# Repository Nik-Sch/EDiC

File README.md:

# EDiC - Educational Digital Computer
SystemVerilog simulation of an 8 bit discrete TTL CPU I am building for fun. The final CPU will be similar to Ben Eaters Project with some differences and the following features:
- I printed prototype PCBs that reassembles 830 Breadboards with some improvements.
- Two general purpose registers.
- ALU with `add/sub`, `AND`, `XOR` and left/right shift operations
- 512 byte instruction EEPROM (256 byte instruction, 256 immediate values)
- 256 byte program SRAM
- 8bit input and output registers

Full documentation is available as my [masters thesis](thesis/thesis.pdf).

## Update 08.03.2022 - EDiC is finished
The EDiC is finished and plays snake ;)

## Update 25.10.2021 - new name - new future
This project is getting a revival as I am rebuilding it with a few key changes and improvements.
It will get a real clock, one big multilayer PCB and stack pointer, 16bit ram/rom addressing and a lot more.

## Update 21.01.2021 - 8bit-CPU is finished!
  
- I debugged a lot of tiny bugs todo with writeEnable and especially clockEnable signals
- Mounted all PCBs to look nice

## Update 15.01.2021
<details><summary>First program got executed!</summary>
  
  - I finished building everything and after about a week of endless debugging bugfixing the first program ran correctly.
  - The gif below shows how the CPU executes 6² and outputs the result which is shown in hexadecimal (6²=36=0x24).

</details>

## Update 22.12.2020
<details><summary>Update of the final(ish) layout:</summary>
  
  - I finished and interconnected all of the data path + bus, except for the PC at the bottom.
  - The ALU + regset + SRAM is fully functional with some debugging effort like pulling up all connections to the 5V CMOS SRAM which has an higher voltage requirement for high level inputs.
  - Half of the control logic has wires and I decided to swap the two control boards for better interconnection.

</details>

## Update 13.12.2020
<details><summary>First picture of the final(ish) layout:</summary>
  
  - On top of all boards is the clock module which is basically the clock module by Ben Eater with 555 timers which features an automatic clock which speed is settable by a potentiometer an a manual, debounced clock pulse with a push button. I also added an SR latch for a halt signal which is resettable by a push button to be used as input to the CPU.
  - Red shows the ALU with two 4 bit adders on the left side (with one aluOp MUX. The top right board is a variable width shifter build with three 8 bit MUXs.
  For enabling left/right shift the last ALU board includes two MUXs to reverse the input and the final two aluOp MUXs.
  - Purple shows the register set on the left with a MUX for the A input of the ALU and one MUX + Tristate Transceiver to the bus.
  The bottom board will include LEDs for the registers and the right board includes aluOut register + Tristate, LEDs and register clock enable logic.
  - The blue encircled board contains the RAM module with an memory address register, the sockeled instruction EEPROM + SRAM.
  - Green will be the control logic with two instruction decode EEPROMs (for 16 control bits) + instruction register on the left.
  The right board includes a 4bit step register for the multicycle control + incrementor (4bit half adder) + logic for external control signals like the halt signal.
  - The orange boards finally include the program counter + incrementor + Tristate Transceiver and load from bus MUX.

</details>

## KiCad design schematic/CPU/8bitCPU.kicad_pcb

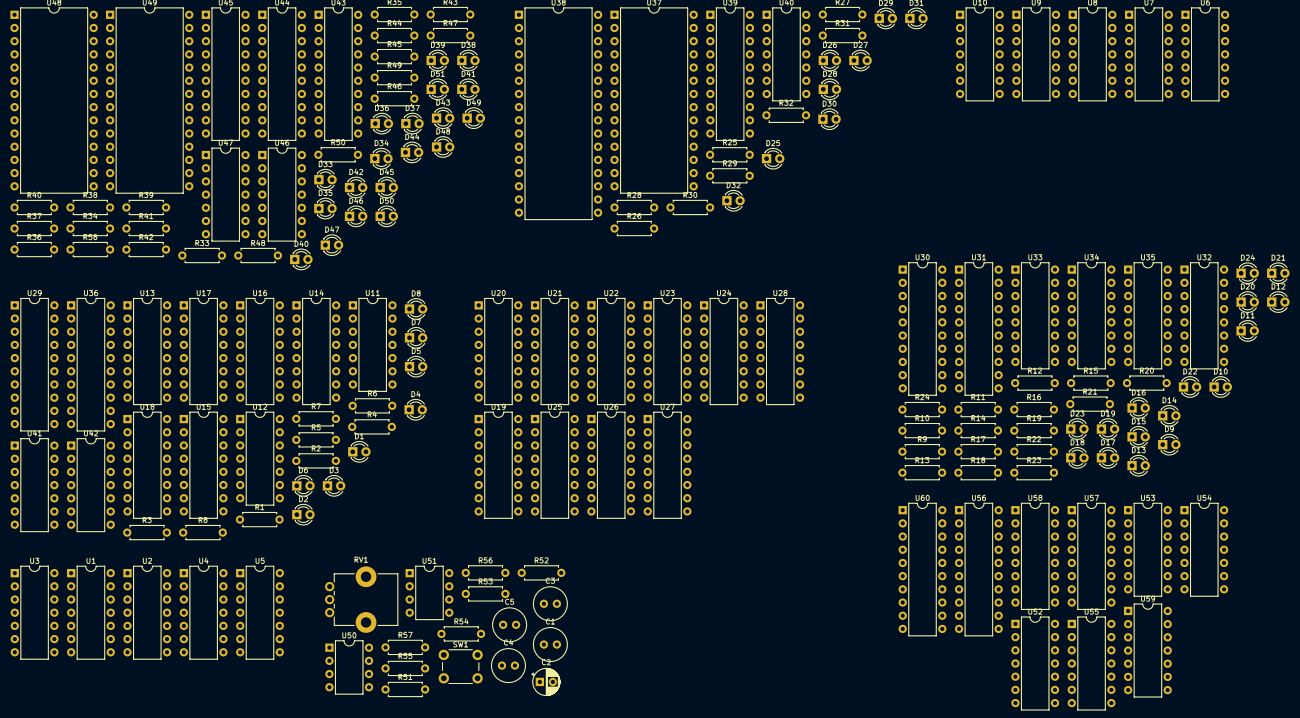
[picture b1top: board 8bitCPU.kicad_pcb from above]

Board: 2 copper layers, 176 parts (0 on the bottom side), 306 nets, no tracks yet.

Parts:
C1, C3: 0.01u; C_Radial_D6.3mm_H5.0mm_P2.50mm
C2: 0.1u; CP_Radial_D5.0mm_P2.50mm
C4, C5: 0.1u; C_Radial_D6.3mm_H5.0mm_P2.50mm
D1, D2, D3, D4, D5, D6, D7, D8, D9, D10, D11, D12, D13, D14, D15, D16, D17, D18, D19, D20, D21, D22, D23, D24, D25, D26, D27, D28, D29, D30, D31, D32, D45, D47, D48, D49, D50: LED; LED_D3.0mm
D33, D51: instrNWE; LED_D3.0mm
D34: instrSel; LED_D3.0mm
D35: aluNOE; LED_D3.0mm
D36: aluYNWE; LED_D3.0mm
D37: reg0NWE; LED_D3.0mm
D38: reg1NWE; LED_D3.0mm
D39: regBusSel; LED_D3.0mm
D40: regBusNOE; LED_D3.0mm
D41: aluSel; LED_D3.0mm
D42: marNWE; LED_D3.0mm
D43: ramWE; LED_D3.0mm
D44: ramOE; LED_D3.0mm
D46: ramSelect; LED_D3.0mm
R1, R2, R3, R4, R5, R6, R7, R8, R9, R10, R11, R12, R13, R14, R15, R16, R17, R18, R19, R20, R21, R22, R23, R24, R25, R26, R27, R28, R29, R30, R31, R32, R33, R34, R35, R36, R37, R38, R39, R40, R41, R42, R43, R44, R45, R46, R47, R48, R49, R50, R52, R53, R54, R57, R58: 1k; R_Axial_DIN0207_L6.3mm_D2.5mm_P7.62mm_Horizontal
R51, R55: 10M; R_Axial_DIN0207_L6.3mm_D2.5mm_P7.62mm_Horizontal
R56: 1M; R_Axial_DIN0207_L6.3mm_D2.5mm_P7.62mm_Horizontal
RV1: 1M; Potentiometer_Bourns_PTV09A-1_Single_Vertical
SW1: SW_Push; SW_PUSH_6mm
U1, U3, U6, U8, U11, U12, U47, U52, U54: 74LS86; DIP-14_W7.62mm
U2, U4, U7, U9, U46, U53, U55: 74LS08; DIP-14_W7.62mm
U5, U10, U41, U42, U59: 74LS32; DIP-14_W7.62mm
U13, U14, U15, U16, U17, U18, U19, U20, U21, U22, U23, U24, U25, U26, U27, U28, U32, U33, U57, U58: 74LS157; DIP-16_W7.62mm
U29, U30, U31, U39, U43: 74LS377; DIP-20_W7.62mm
U34, U35: 74LS257; DIP-16_W7.62mm
U36, U60: 74LS245; DIP-20_W7.62mm
U37, U48, U49: 28C64; DIP-28_W15.24mm
U38: AS6C1008-55PCN; DIP-32_W15.24mm
U40: 74LS00; DIP-14_W7.62mm
U44, U45, U56: 74LS273; DIP-20_W7.62mm
U50, U51: NA555P; DIP-8_W7.62mm

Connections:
/Alu/Adder0/Bit1/Cin: U3.4, U4.4, U5.3
/Alu/Adder0/Bit2/Cin: U3.9, U4.9, U5.6
/Alu/Adder0/Bit3/Cin: U3.12, U4.12, U5.8
/Alu/Adder0/b0: U1.2, U2.2, U11.3
/Alu/Adder0/b1: U1.5, U2.5, U11.6
/Alu/Adder0/b2: U1.10, U2.10, U11.8
/Alu/Adder0/b3: U1.13, U2.13, U11.11
/Alu/Adder1/Bit1/Cin: U8.4, U9.4, U10.3
/Alu/Adder1/Bit2/Cin: U8.9, U9.9, U10.6
/Alu/Adder1/Bit3/Cin: U8.12, U9.12, U10.8
/Alu/Adder1/Cin: U5.11, U8.1, U9.1
/Alu/Adder1/b0: U6.2, U7.2, U12.3
/Alu/Adder1/b1: U6.5, U7.5, U12.6
/Alu/Adder1/b2: U6.10, U7.10, U12.8
/Alu/Adder1/b3: U6.13, U7.13, U12.11
/Alu/a0: U1.1, U2.1, U19.2, U20.13, U32.4
/Alu/a1: U1.4, U2.4, U19.5, U20.10, U32.7
/Alu/a2: U1.9, U2.9, U19.11, U20.6, U32.9
/Alu/a3: U1.12, U2.12, U19.14, U20.3, U32.12
/Alu/a4: U6.1, U7.1, U19.13, U20.2, U33.4
/Alu/a5: U6.4, U7.4, U19.10, U20.5, U33.7
/Alu/a6: U6.9, U7.9, U19.6, U20.11, U33.9
/Alu/a7: U6.12, U7.12, U19.3, U20.14, U33.12
/Alu/adderY0: U3.3, U13.2
/Alu/adderY1: U3.6, U13.5
/Alu/adderY2: U3.8, U13.11
/Alu/adderY3: U3.11, U13.14
/Alu/adderY4: U8.3, U14.2
/Alu/adderY5: U8.6, U14.5
/Alu/adderY6: U8.8, U14.11
/Alu/adderY7: U8.11, U14.14
/Alu/and0: U2.3, U5.1, U13.3
/Alu/and1: U2.6, U5.4, U13.6
/Alu/and2: U2.8, U5.9, U13.10
/Alu/and3: U2.11, U5.12, U13.13
/Alu/and4: U7.3, U10.1, U14.3
/Alu/and5: U7.6, U10.4, U14.6
/Alu/and6: U7.8, U10.9, U14.10
/Alu/and7: U7.11, U10.12, U14.13
/Alu/shifter/y0: U15.3, U27.4
/Alu/shifter/y1: U15.6, U27.7
/Alu/shifter/y2: U15.10, U27.9
/Alu/shifter/y3: U15.13, U27.12
/Alu/shifter/y4: U16.3, U28.4
/Alu/shifter/y5: U16.6, U28.7
/Alu/shifter/y6: U16.10, U28.9
/Alu/shifter/y7: U16.13, U28.12
/Alu/xor0: U1.3, U3.2, U4.2, U15.2
/Alu/xor1: U1.6, U3.5, U4.5, U15.5
/Alu/xor2: U1.8, U3.10, U4.10, U15.11
/Alu/xor3: U1.11, U3.13, U4.13, U15.14
/Alu/xor4: U6.3, U8.2, U9.2, U16.2
/Alu/xor5: U6.6, U8.5, U9.5, U16.5
/Alu/xor6: U6.8, U8.10, U9.10, U16.11
/Alu/xor7: U6.11, U8.13, U9.13, U16.14
/bus0: U11.1, U21.1, U22.1, U30.3, U31.3, U34.4, U36.18, U37.11, U38.13, U39.3, U43.3, U57.3, U60.18
/bus1: U11.4, U23.1, U24.1, U30.4, U31.4, U34.7, U36.17, U37.12, U38.14, U39.4, U43.4, U57.6, U60.17
/bus2: U11.9, U25.1, U26.1, U30.7, U31.7, U34.12, U36.16, U37.13, U38.15, U39.7, U43.7, U57.10, U60.16
/bus3: U11.12, U30.8, U31.8, U34.9, U36.15, U37.15, U38.17, U39.8, U43.8, U57.13, U60.15
/bus4: U12.1, U30.13, U31.13, U35.4, U36.14, U37.16, U38.18, U39.13, U43.13, U58.3, U60.14
/bus5: U12.4, U30.14, U31.14, U35.7, U36.13, U37.17, U38.19, U39.14, U43.14, U58.6, U60.13
/bus6: U12.9, U30.17, U31.17, U35.12, U36.12, U37.18, U38.20, U39.17, U43.17, U58.10, U60.12
/bus7: U12.12, U30.18, U31.18, U35.9, U36.11, U37.19, U38.21, U39.18, U43.18, U58.13, U60.11
/clock/clk0: R51.2, U51.3
/clock/clk1: R55.2, U50.3
/control/a0: U44.2, U46.1, U46.9, U47.2, U47.4, U48.10, U49.10
/control/a1: U44.5, U46.2, U47.5, U48.9, U49.9
/control/a2: U44.6, U47.9, U47.13, U48.8, U49.8
/control/a6: U45.9, U48.4, U49.4
/control/a7: U45.12, U48.3, U49.3
/control/a8: U45.15, U48.25, U49.25
/control/a9: U45.16, U48.24, U49.24
/control/a10: U45.19, U48.21, U49.21
/control/a11: U44.12, U48.23, U49.23
/control/a12: U44.9, U48.2, U49.2
/pc/pc0: U52.2, U52.4, U53.1, U56.2, U60.2
/pc/pc1: U52.5, U53.2, U56.5, U60.3
/pc/pc2: U52.10, U53.5, U56.6, U60.4
/pc/pc3: U52.13, U53.10, U56.9, U60.5
/pc/pc4: U53.13, U54.2, U56.12, U60.6
/pc/pc5: U54.5, U55.2, U56.15, U60.7
/pc/pc6: U54.10, U55.5, U56.16, U60.8
/pc/pc7: U54.13, U56.19, U60.9
/ram/ramNOE: U38.24, U40.8
/ram/ramNWE: U38.29, U40.3
/ram/romNOE: U37.22, U40.11
/regset/r00: R9.2, U30.2, U32.2, U34.2
/regset/r01: R10.2, U30.5, U32.5, U34.5
/regset/r02: R11.2, U30.6, U32.11, U34.14
/regset/r03: R12.2, U30.9, U32.14, U34.11
/regset/r04: R13.2, U30.12, U33.2, U35.2
/regset/r05: R14.2, U30.15, U33.5, U35.5
/regset/r06: R15.2, U30.16, U33.11, U35.14
/regset/r07: R16.2, U30.19, U33.14, U35.11
/regset/r10: R17.2, U31.2, U32.3, U34.3
/regset/r11: R18.2, U31.5, U32.6, U34.6
/regset/r12: R19.2, U31.6, U32.10, U34.13
/regset/r13: R20.2, U31.9, U32.13, U34.10
/regset/r14: R21.2, U31.12, U33.3, U35.3
/regset/r15: R22.2, U31.15, U33.6, U35.6
/regset/r16: R23.2, U31.16, U33.10, U35.13
/regset/r17: R24.2, U31.19, U33.13, U35.10
GND: C1.2, C2.2, C3.2, C5.1, D1.1, D2.1, D3.1, D4.1, D5.1, D6.1, D7.1, D8.1, D9.1, D10.1, D11.1, D12.1, D13.1, D14.1, D15.1, D16.1, D17.1, D18.1, D19.1, D20.1, D21.1, D22.1, D23.1, D24.1, D25.1, D26.1, D27.1, D28.1, D29.1, D30.1, D31.1, D32.1, D33.1, D34.1, D35.1, D36.1, D37.1, D38.1, D39.1, D40.1, D41.1, D42.1, D43.1, D44.1, D45.1, D46.1, D47.1, D48.1, D49.1, D50.1, D51.1, SW1.1, U1.7, U2.7, U3.7, U4.7, U5.7, U6.7, U7.7, U8.7, U9.7, U10.7, U11.7, U12.7, U13.8, U13.15, U14.8, U14.15, U15.8, U15.15, U16.8, U16.15, U17.8, U17.15, U18.8, U18.15, U19.8, U19.15, U20.8, U20.15, U21.8, U21.15, U22.8, U22.13, U22.15, U23.8, U23.15, U24.8, U24.10, U24.13, U24.15, U25.8, U25.15, U26.3, U26.6, U26.8, U26.10, U26.13, U26.15, U27.8, U27.15, U28.8, U28.15, U29.10, U30.10, U31.10, U32.8, U32.15, U33.8, U33.15, U34.8, U35.8, U36.10, U37.2, U37.14, U37.20, U37.21, U37.23, U37.24, U38.2, U38.3, U38.4, U38.16, U38.22, U38.23, U38.25, U38.26, U38.27, U38.28, U38.31, U39.10, U40.7, U41.7, U41.12, U41.13, U42.7, U43.10, U44.10, U44.14, U44.17, U44.18, U45.10, U46.7, U46.12, U46.13, U47.7, U48.14, U48.20, U48.22, U49.14, U49.20, U49.22, U50.1, U51.1, U52.7, U53.7, U54.7, U55.7, U55.12, U55.13, U56.10, U57.8, U57.15, U58.8, U58.15, U59.4, U59.5, U59.7, U59.9, U59.10, U59.12, U59.13, U60.10
unnamed: C1.1, U51.5
unnamed: C2.1, RV1.3, U51.2, U51.6
unnamed: C3.1, U50.5
unnamed: C4.1, R54.2, U50.2
unnamed: C4.2, R53.2, SW1.2
unnamed: C5.2, R56.2, U50.6, U50.7
unnamed: D1.2, R1.1
unnamed: D2.2, R2.1
unnamed: D3.2, R3.1
unnamed: D4.2, R4.1
unnamed: D5.2, R5.1
unnamed: D6.2, R6.1
unnamed: D7.2, R7.1
unnamed: D8.2, R8.1
unnamed: D9.2, R9.1
unnamed: D10.2, R10.1
unnamed: D11.2, R11.1
unnamed: D12.2, R12.1
unnamed: D13.2, R13.1
unnamed: D14.2, R14.1
unnamed: D15.2, R15.1
unnamed: D16.2, R16.1
unnamed: D17.2, R17.1
unnamed: D18.2, R18.1
unnamed: D19.2, R19.1
unnamed: D20.2, R20.1
unnamed: D21.2, R21.1
unnamed: D22.2, R22.1
unnamed: D23.2, R23.1
unnamed: D24.2, R24.1
unnamed: D25.2, R25.1
unnamed: D26.2, R26.1
unnamed: D27.2, R27.1
unnamed: D28.2, R28.1
unnamed: D29.2, R29.1
unnamed: D30.2, R30.1
unnamed: D31.2, R31.1
unnamed: D32.2, R32.1
unnamed: D33.2, R33.1
unnamed: D34.2, R34.1
unnamed: D35.2, R35.1
unnamed: D36.2, R36.1
unnamed: D37.2, R37.1
unnamed: D38.2, R38.1
unnamed: D39.2, R39.1
unnamed: D40.2, R40.1
unnamed: D41.2, R41.1
unnamed: D42.2, R42.1
unnamed: D43.2, R43.1
unnamed: D44.2, R44.1
unnamed: D45.2, R45.1
unnamed: D46.2, R46.1
unnamed: D47.2, R47.1
unnamed: D48.2, R48.1
unnamed: D49.2, R49.1
unnamed: D50.2, R50.1
unnamed: D51.2, R58.1
unnamed: R2.2, U29.16, U36.8, U41.10
unnamed: R3.2, U29.15, U36.7, U41.5
unnamed: R4.2, U29.12, U36.6, U41.2
unnamed: R5.2, U29.9, U36.5, U42.13
unnamed: R6.2, U29.6, U36.4, U42.10
unnamed: R7.2, U29.5, U36.3, U42.5
unnamed: R8.2, U29.2, U36.2, U42.2
unnamed: R25.2, U37.3, U38.5, U39.19
unnamed: R26.2, U37.4, U38.6, U39.16
unnamed: R27.2, U37.5, U38.7, U39.15
unnamed: R28.2, U37.6, U38.8, U39.12
unnamed: R29.2, U37.7, U38.9, U39.9
unnamed: R30.2, U37.8, U38.10, U39.6
unnamed: R31.2, U37.9, U38.11, U39.5
unnamed: R32.2, U37.10, U38.12, U39.2
unnamed: R52.1, R57.2, U51.7
unnamed: R52.2, RV1.2
unnamed: U4.3, U5.2
unnamed: U4.6, U5.5
unnamed: U4.8, U5.10
unnamed: U4.11, U5.13
unnamed: U9.3, U10.2
unnamed: U9.6, U10.5
unnamed: U9.8, U10.10
unnamed: U9.11, U10.13
unnamed: U13.4, U17.2
unnamed: U13.7, U17.5
unnamed: U13.9, U17.11
unnamed: U13.12, U17.14
unnamed: U14.4, U18.2
unnamed: U14.7, U18.5
unnamed: U14.9, U18.11
unnamed: U14.12, U18.14
unnamed: U15.4, U17.3
unnamed: U15.7, U17.6
unnamed: U15.9, U17.10
unnamed: U15.12, U17.13
unnamed: U16.4, U18.3
unnamed: U16.7, U18.6
unnamed: U16.9, U18.10
unnamed: U16.12, U18.13
unnamed: U17.4, U29.3
unnamed: U17.7, U29.4
unnamed: U17.9, U29.7
unnamed: U17.12, U29.8
unnamed: U18.4, U29.13
unnamed: U18.7, U29.14
unnamed: U18.9, U29.17
unnamed: U18.12, U29.18
unnamed: U19.4, U21.2
unnamed: U19.7, U21.3, U21.5
unnamed: U19.9, U21.6, U21.11
unnamed: U19.12, U21.10, U21.14
unnamed: U20.4, U21.13, U22.2
unnamed: U20.7, U22.3, U22.5
unnamed: U20.9, U22.6, U22.11
unnamed: U20.12, U22.10, U22.14
unnamed: U21.4, U23.2
unnamed: U21.7, U23.5
unnamed: U21.9, U23.3, U23.11
unnamed: U21.12, U23.6, U23.14
unnamed: U22.4, U23.10, U24.2
unnamed: U22.7, U23.13, U24.5
unnamed: U22.9, U24.3, U24.11
unnamed: U22.12, U24.6, U24.14
unnamed: U23.4, U25.2
unnamed: U23.7, U25.5
unnamed: U23.9, U25.11
unnamed: U23.12, U25.14
unnamed: U24.4, U25.3, U26.2
unnamed: U24.7, U25.6, U26.5
unnamed: U24.9, U25.10, U26.11
unnamed: U24.12, U25.13, U26.14
unnamed: U25.4, U27.2, U28.13
unnamed: U25.7, U27.5, U28.10
unnamed: U25.9, U27.11, U28.6
unnamed: U25.12, U27.14, U28.3
unnamed: U26.4, U27.13, U28.2
unnamed: U26.7, U27.10, U28.5
unnamed: U26.9, U27.6, U28.11
unnamed: U26.12, U27.3, U28.14
unnamed: U40.6, U40.9
unnamed: U41.1, U41.6
unnamed: U41.3, U42.12
unnamed: U41.4, U41.8
unnamed: U42.1, U42.6
unnamed: U42.4, U42.8
unnamed: U42.9, U42.11
unnamed: U43.2, U45.3
unnamed: U43.5, U45.4
unnamed: U43.6, U45.7
unnamed: U43.9, U45.8
unnamed: U43.12, U45.13
unnamed: U43.15, U45.14
unnamed: U43.16, U45.17
unnamed: U43.19, U45.18
unnamed: U44.3, U47.3
unnamed: U44.4, U46.10, U47.6
unnamed: U44.7, U47.8
unnamed: U46.3, U47.10
unnamed: U46.4, U47.11
unnamed: U46.5, U46.8
unnamed: U52.3, U57.2
unnamed: U52.6, U57.5
unnamed: U52.8, U57.11
unnamed: U52.9, U53.3, U53.4
unnamed: U52.11, U57.14
unnamed: U52.12, U53.6, U53.9
unnamed: U53.11, U54.4, U55.1
unnamed: U53.8, U53.12, U54.1
unnamed: U54.3, U58.2
unnamed: U54.6, U58.5
unnamed: U54.8, U58.11
unnamed: U54.9, U55.3, U55.4
unnamed: U54.11, U58.14
unnamed: U54.12, U55.6
unnamed: U55.8, U56.11
unnamed: U55.10, U59.3
unnamed: U56.3, U57.4
unnamed: U56.4, U57.7
unnamed: U56.7, U57.9
unnamed: U56.8, U57.12
unnamed: U56.13, U58.4
unnamed: U56.14, U58.7
unnamed: U56.17, U58.9
unnamed: U56.18, U58.12
clk: R51.1, R53.1, R54.1, R55.1, R56.1, R57.1, U1.14, U2.14, U3.14, U4.14, U5.14, U6.14, U7.14, U8.14, U9.14, U10.14, U11.14, U12.14, U13.16, U14.16, U15.16, U16.16, U17.16, U18.16, U19.16, U20.16, U21.16, U22.16, U23.16, U24.16, U25.16, U26.16, U27.16, U28.16, U29.11, U29.20, U30.11, U30.20, U31.11, U31.20, U32.16, U33.16, U34.16, U35.16, U36.1, U36.20, U37.27, U37.28, U38.30, U38.32, U39.11, U39.20, U40.2, U40.14, U41.14, U42.14, U43.11, U43.20, U44.1, U44.11, U44.20, U45.1, U45.11, U45.20, U46.14, U47.1, U47.12, U47.14, U48.27, U48.28, U49.27, U49.28, U50.4, U50.8, U51.4, U51.8, U52.1, U52.14, U53.14, U54.14, U55.9, U55.14, U56.1, U56.20, U57.16, U58.16, U59.14, U60.1, U60.20
ctrlAluNOE: R35.2, U36.19, U48.11
ctrlAluOp0: U17.1, U18.1, U45.5, U48.6, U49.6
ctrlAluOp1: U13.1, U14.1, U15.1, U16.1, U45.6, U48.5, U49.5
ctrlAluSel: R41.2, U32.1, U33.1, U48.18
ctrlAluSub: U3.1, U4.1, U11.2, U11.5, U11.10, U11.13, U12.2, U12.5, U12.10, U12.13, U19.1, U20.1, U27.1, U28.1, U45.2, U48.7, U49.7
ctrlAluYNWE: R36.2, U29.1, U48.12
ctrlInstrNWE: R33.2, R34.2, R58.2, U37.25, U43.1, U46.6, U57.1, U58.1, U59.2
ctrlMarNWE: R42.2, U39.1, U48.19
ctrlPCLoad: R45.2, U49.13, U59.1
ctrlPCNOE: R48.2, U49.17, U60.19
ctrlRamOE: R44.2, U40.10, U40.12, U49.12
ctrlRamSelect: R46.2, U40.4, U40.5, U40.13, U49.15
ctrlRamWE: R43.2, U40.1, U49.11
ctrlReg0NWE: R37.2, U30.1, U48.13
ctrlReg1NWE: R38.2, U31.1, U48.15
ctrlRegBusNOE: R40.2, U34.15, U35.15, U48.17
ctrlRegBusSel: R39.2, U34.1, U35.1, U48.16
flagNZero: U42.3, U44.8
flagNegative: R1.2, U29.19, U36.9, U41.9, U44.13

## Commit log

2020-11-14 git starting, alu works kinda i guess
2020-11-14 writing into registers works over the bus
2020-11-15 shifting and ram access works
2020-11-15 generate controlPath ROM content script
2020-11-15 it does stuff and executed 2 instructions 🎉
2020-11-16 added a "compiler" and immediate instructions
2020-11-18 added kicad schematics and ram instructions
2020-11-20 added arduino nano 8bit to 7seg decoder
2020-11-22 added eeprom programmer
2020-12-11 changed alu reg to y instead of b
2020-12-13 added hlt instruction changed output enable to active low updated ram to use asyncRam and an instruction rom
2020-12-13 zero flag got nonZero and added current image
2020-12-21 upgraded control unit/microcode, now branches and jumps etc.
2020-12-22 continued to improve control logic + asm square implementation working
2020-12-22 readme update
2020-12-22 updated .gitignore
2020-12-22 updated summary
2020-12-25 Added schematic
2021-01-04 7segment code adapted for dip28 atmega328p compile for eeprom programmer control: step register on falling edge
2021-01-14 cpu works in ttl
2021-01-15 incorporated hardware fixes
2021-01-17 changed immediates
    immediates are now stored in a second byte of the instruction and can therefore be full 8 bit
2021-01-17 simplified square.s and stuff
2021-01-18 immediate values are now in instrRom [256]-[511]
    with this, always 256 instructions are available
2021-01-18 added labels, renamed simulation roms and swapped incrPC ctrol signal back
2021-01-20 finished hardware and implemented integer factorization
2021-01-20 starting kicad version
2021-01-23 pcbVersion: kicad alu design
2021-01-24 pcbVersion: regset + alu
2021-01-28 pcbversion: ram, started pc
2021-01-30 pcbVersion: kinda done
2021-03-30 final update for 8bit
2021-05-15 schematic
2021-07-31 schematic finished
2021-07-31 schematic zip
2021-08-02 updated schematic
2021-09-23 pre upgrade to vivado 2021
2021-09-24 fibonacci works again with new memory design
2021-09-25 schematic with henry
2021-10-01 updated verilog from schematic
2021-10-25 updated some more verilog
2021-10-25 renamed project
2021-10-25 fibonacci works again, sp etc needs to be tested
2021-10-31 fixed a lot of smaller bugs, function call and return works now
    factorization and fibonacci implemented
2021-11-01 reworked instructions and calling convention
2021-11-01 added pdf
2021-11-05 7seg displayDriver, emulated 3-state, synthesis
2021-11-06 upgraded to vivado 2021.2
2021-11-14 asm: added constants tb: simulate with 100MHz/5MHz clocks as in synth + increment switches now and then
2021-11-14 simulated
2021-11-14 pointers (setting mar1 + r := [s] + [s] := r instructions
2021-11-19 works on the fpga 🎉
2021-11-21 debugged debugging
2021-11-21 debugger works + show pc, step and r0, r1 on devBoard
2021-11-22 prng + snake in python + bug carry fix in alu
2021-11-26 added string constants in ram
2021-11-26 added uart expansion card
2021-11-27 snaky snake started and some bugs fixed
2021-11-28 schematic: alu/shifter carry fix
2021-11-29 snake finished?
2021-11-29 fixed uart_rx and snake
2021-11-30 snake no full redrawing
2021-11-30 started with schematic poster
2021-11-30 logos
2021-12-01 reposition in poster
2021-12-01 kicad 6
2021-12-03 poster passed erc, check
2021-12-03 started anotating poster
2021-12-06 restructured folders
2021-12-06 started with netlist to verilog
2021-12-11 netlist2verilog converter started
2021-12-13 netlist simulation works
2021-12-22 ttl fpga: factorization works in sim and fpga
2021-12-26 io: async register + reversed bus
2021-12-27 critical path calculations
2021-12-28 carry flag + ram critical path
2022-01-03 verifying ttl cpu instruction for instruction with test.s
2022-01-05 finished test code for netlist simulation
2022-01-05 orcad exported netlist
2022-01-07 orcad exported netlist works
2022-01-10 snake debugging, fixed bug in the netlist
2022-01-15 final netlist simulation + ram address setup cycle in microcode
2022-01-18 synth on windows
2022-01-19 singal testing board top
2022-01-26 uart 16c550.s
2022-01-29 snake works with uart io card
    include directive for assembler
2022-02-03 snake works with vt100
    vt100 is slow with cursor movements -> xon/xoff or fill null bytes must be transferred
    vivado sucks -> windows project which is identical but works on win
2022-03-06 binary microcode
2022-03-06 binary instructionRom
2022-03-06 inbetriebnahme
2022-03-07 test1
2022-03-07 Inbetriebnahme Day 2
2022-03-08 fixed the return bug, snake is running
2022-03-08 fix for buggy uart chip
2022-03-11 template for thesis
2022-03-11 logos and makefile
2022-04-20 toc and some text
2022-04-22 alu figures, modules finished
2022-04-26 previous work
2022-04-28 started with design adaptations
2022-05-10 design adaptations
2022-05-16 microcode
2022-05-16 assembler
2022-05-17 restructuring
2022-05-20 merged old chapters 2 and 3
2022-05-23 assembler continued
2022-05-23 finished software
2022-05-23 fpga
2022-06-02 addded notes and images
2022-06-07 fpga simulation
2022-06-08 fpga continued
2022-06-08 timing analysis
2022-06-09 hardware
2022-06-09 control signals
2022-06-10 chapter 6
2022-06-11 final bug
2022-06-11 short names in toc
2022-06-21 introduction
2022-06-21 proof read chapters 1-4
2022-06-22 proof reading of chapter 5 and 6
2022-06-22 abstract
2022-06-24 conclusion
2022-06-30 ltex grammar checking
2022-07-04 a lot of typos
2022-07-04 typos
2022-07-04 typos + schematics
2022-07-07 magnetic field, ee-stuff
2022-07-11 image of pcbs
2022-07-12 rm clear/set register image
2022-07-12 some typos
2022-07-12 lost!=won
2022-07-12 final?
2022-09-26 added rewiring changes
2022-09-26 moved sim_ttl vivado project to an tcl script
2022-09-26 fixed A7 in the netlist
2022-10-09 cleanup
2022-10-09 starting conversion to vhdl
2022-10-23 fpga kind of working again, pc stays at 0, however
2022-10-23 fixed problems in 74x867
    snake works again
2022-10-23 Vhdl conversion (#1)
    * starting conversion to vhdl
    * fpga kind of working again, pc stays at 0, however
    * fixed problems in 74x867
    snake works again
2022-10-26 starting with uart debugger
2022-10-30 simulating board top instead of generated
2023-01-25 added datapath drawings for talk
